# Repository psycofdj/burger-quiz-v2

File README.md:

<!-- markdown-toc start - Don't edit this section. Run M-x markdown-toc-refresh-toc -->
**Table of Contents**

- [Hardware](#hardware)
    - [Global Schematics](#global-schematics)
    - [Ready to solder PCB](#ready-to-solder-pcb)
- [Construction](#construction)
    - [Global design](#global-design)
    - [Components](#components)
- [Installation](#installation)

<!-- markdown-toc end -->

## Hardware

### Global Schematics

Sources for global schematics are [here](./kicad/board)

### Ready to solder PCB

Sources for ready-to-solder PCB are [here](./kicad/pcb)

## Construction

### Global design

Sources for desk design are [here](./sketcup)

### Components

- 22.99€,  3 x LCD displays: https://www.amazon.fr/dp/B07V5K3ZVB?ref=ppx_yo2ov_dt_b_product_details&th=1
- 8.99€,  15 x 3.3V to 5V signal converter: https://www.amazon.fr/dp/B082F6BSB5?psc=1&ref=ppx_yo2ov_dt_b_product_details
- 8.58€,   1 x LED kit: https://www.amazon.fr/dp/B08S2W74K7?ref=ppx_yo2ov_dt_b_product_details&th=1
- 10.99€,  1 x Flat cable: https://www.amazon.fr/dp/B082WZC56B?psc=1&ref=ppx_yo2ov_dt_b_product_details
- 11.99€,  1 x Connector kit: https://www.amazon.fr/dp/B089LZ14WB?psc=1&ref=ppx_yo2ov_dt_b_product_details
- 66.50€,  1 x Rasberry PI 4 model B: https://www.kubii.com/en/raspberry-pi-boards/2772-raspberry-pi-4-model-b-4gb-3272496309333.html
- 7,49 €,  1 x 16GB microSD: https://www.amazon.fr/dp/B07DVG12SF?psc=1&ref=ppx_yo2ov_dt_b_product_details
- 18.59€,  1 x USB Speader: https://www.amazon.fr/Umitive-Haut-Parleur-dOrdinateur-Compatibilit%C3%A9-Antid%C3%A9rapante/dp/B08JTRML6R/ref=sr_1_7?keywords=enceinte+usb&qid=1697275415&sr=8-7
- 38,27€, 13 x Custom made 5v LED push switches: https://fr.aliexpress.com/item/4000098893464.html?spm=a2g0o.order_list.order_list_main.10.21ef5e5b7tX8DX&gatewayAdapt=glo2fra

## Installation

Sources for software are [here](./bquiz)

- Enable primary I2C port (/dev/i2c-1)

```
$ sudo raspi-config
(select 3. Interface options)
(select I5. I2C)
(select yes)
```

- Enable secondary I2C port (/dev/i2c-0)

```
cat /boot/config.txt
...
dtparam=i2c_arm=on
dtparam=i2c_vc=on
...
```

- Check I2C ports

```
 # package to test gpio port
 sudo apt install i2c-dev i2c-tools

 # check i2c ports, should have 27 on
 i2cdetect -y 1
 i2cdetect -y 0
```

- Install sound support

```
 sudo apt-get install pulseaudio pulseaudio-utils python3-vlc
```

- Configure default pulseaudio sink

```
 pactl set-default-sink alsa_output.usb-C-Media_Electronics_Inc._USB_Audio_Device-00.analog-stereo
```

- Install software as user startup service

```
 # install bquiz cli to ~/.local/bin
 python3 -m pip install .

 # install user systemd unit
 mkdir -p ~/.config/systemd/user
 ln -s $(pwd)/systemd/user/bquiz.service ~/.config/systemd/
 systemctl --user enable bquiz.service

 # run bquiz
 systemctl --user start bquiz.service
```

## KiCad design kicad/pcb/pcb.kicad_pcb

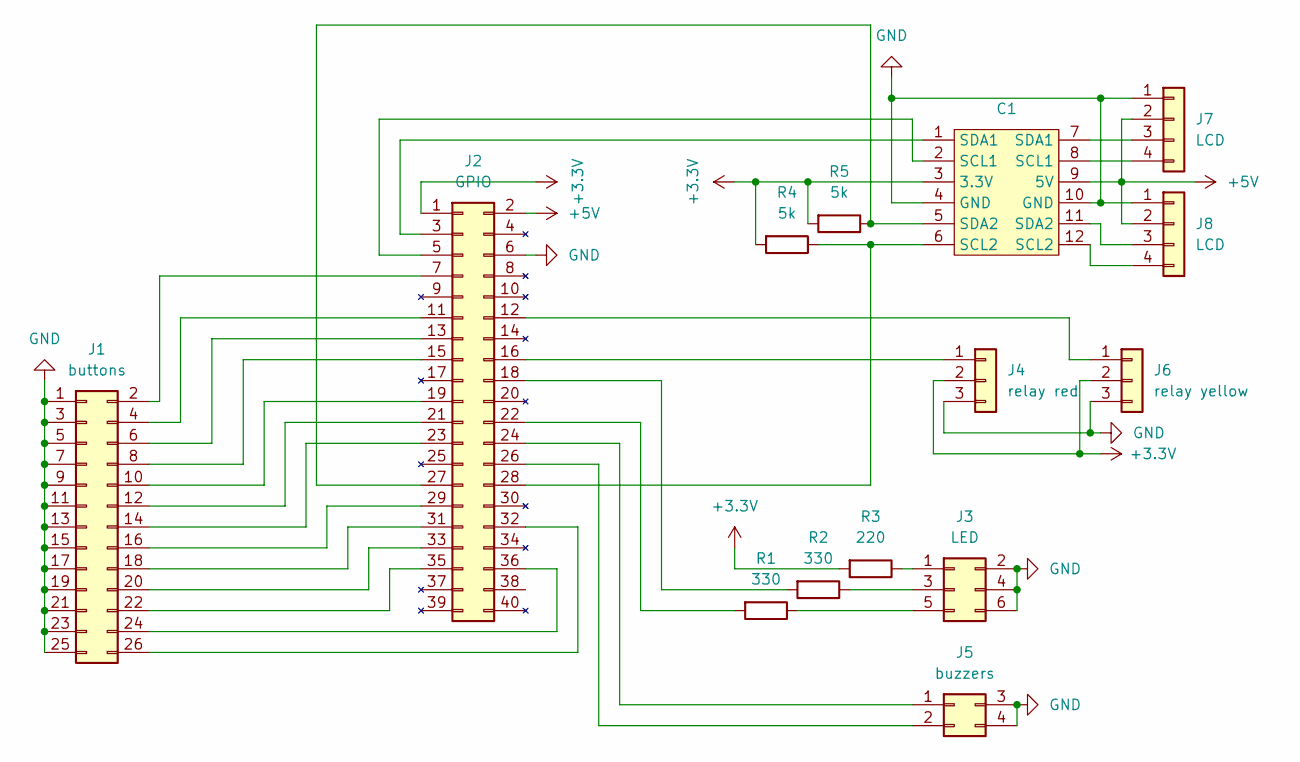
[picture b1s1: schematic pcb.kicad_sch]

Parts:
C1: Converter_3.3v_5v_i2c
J1: buttons; PinHeader_2x13_P2.54mm_Vertical
J2: GPIO; PinSocket_2x20_P2.54mm_Vertical
J3: LED; PinHeader_2x03_P2.54mm_Vertical
J4: relay red; PinHeader_1x03_P2.54mm_Vertical
J5: buzzers; PinHeader_2x02_P2.54mm_Vertical
J6: relay yellow; PinHeader_1x03_P2.54mm_Vertical
J7, J8: LCD; PinHeader_1x04_P2.54mm_Vertical
R1, R2: 330; R_Axial_DIN0204_L3.6mm_D1.6mm_P2.54mm_Vertical
R3: 220; R_Axial_DIN0204_L3.6mm_D1.6mm_P2.54mm_Vertical
R4, R5: 5k; R_Axial_DIN0204_L3.6mm_D1.6mm_P2.54mm_Vertical

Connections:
+3.3V: C1.3 (3.3V), J2.1 (3v3), J4.2, J6.2, R3.2, R4.2, R5.2
+5V: C1.9 (5V), J2.2 (5v0), J7.2 (VCC), J8.2 (VCC)
GND: C1.4 (GND), C1.10 (GND), J1.1 (reset), J1.3 (red+), J1.5 (red-), J1.7 (yellow+), J1.9 (yellow-), J1.11 (nuggets), J1.13 (selpoivre), J1.15 (menus), J1.17 (addition), J1.19 (sample1), J1.21 (sample2), J1.23 (sample3), J1.25 (sample4), J2.6 (GND), J3.2, J3.4, J3.6, J4.3, J5.3, J5.4, J6.3, J7.1 (GND), J8.1 (GND)
unnamed: C1.2 (SCL1), J2.5 (SCL1)
unnamed: C1.6 (SCL2), J2.28 (SCL2), R4.1
unnamed: C1.1 (SDA1), J2.3 (SDA1)
unnamed: C1.5 (SDA2), J2.27 (SDA2), R5.1
unnamed: J1.14 (selpoivre), J2.23 (wip14)
unnamed: J1.16 (menus), J2.29 (wip21)
unnamed: J1.18 (addition), J2.31 (wip22)
unnamed: J1.20 (sample1), J2.33 (wip23)
unnamed: J1.22 (sample2), J2.35 (wip24)
unnamed: J1.4 (red+), J2.11 (wpi0)
unnamed: J2.12 (wpi1), J6.1
unnamed: J1.6 (red-), J2.13 (wpi2)
unnamed: J1.8 (yellow+), J2.15 (wpi3)
unnamed: J2.16 (wpi4), J4.1
unnamed: J2.18 (wpi5), R2.2
unnamed: J2.22 (wpi6), R1.2
unnamed: J1.2 (reset), J2.7 (wpi7)
unnamed: J2.24 (wpi10), J5.1
unnamed: J2.26 (wpi11), J5.2
unnamed: J1.10 (yellow-), J2.19 (wpi12)
unnamed: J1.12 (nuggets), J2.21 (wpi13)
unnamed: J1.26 (sample4), J2.32 (wpi26)
unnamed: J1.24 (sample3), J2.36 (wpi27)
unnamed: J3.1, R3.1
unnamed: J3.3, R2.1
unnamed: J3.5, R1.1
unnamed: C1.8 (SCL1), J7.4 (SCL)
unnamed: C1.7 (SDA1), J7.3 (SDA)
unnamed: C1.12 (SCL2), J8.4 (SCL)
unnamed: C1.11 (SDA2), J8.3 (SDA)

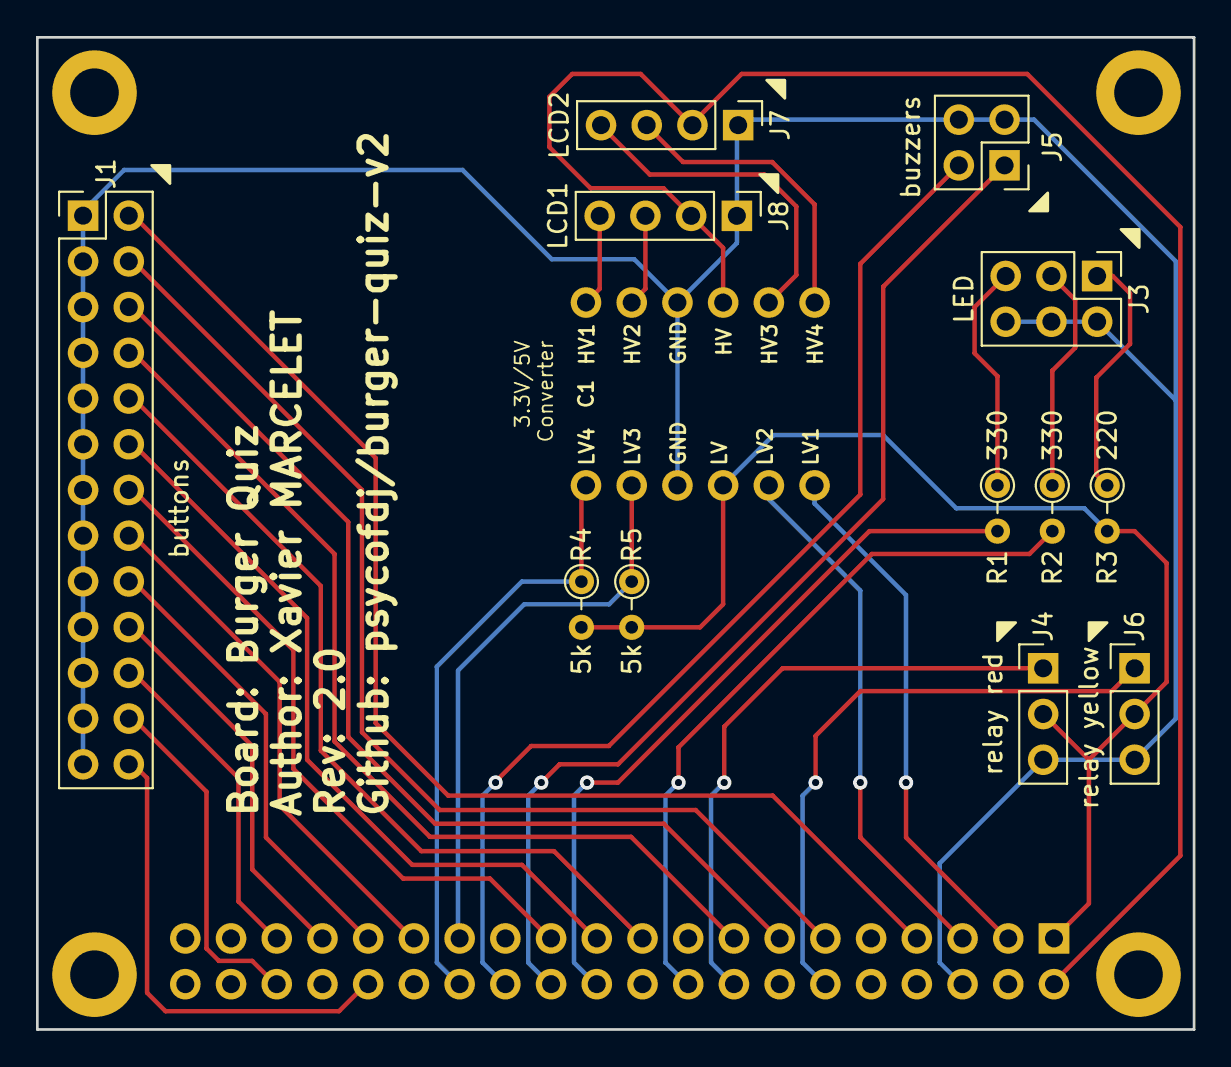
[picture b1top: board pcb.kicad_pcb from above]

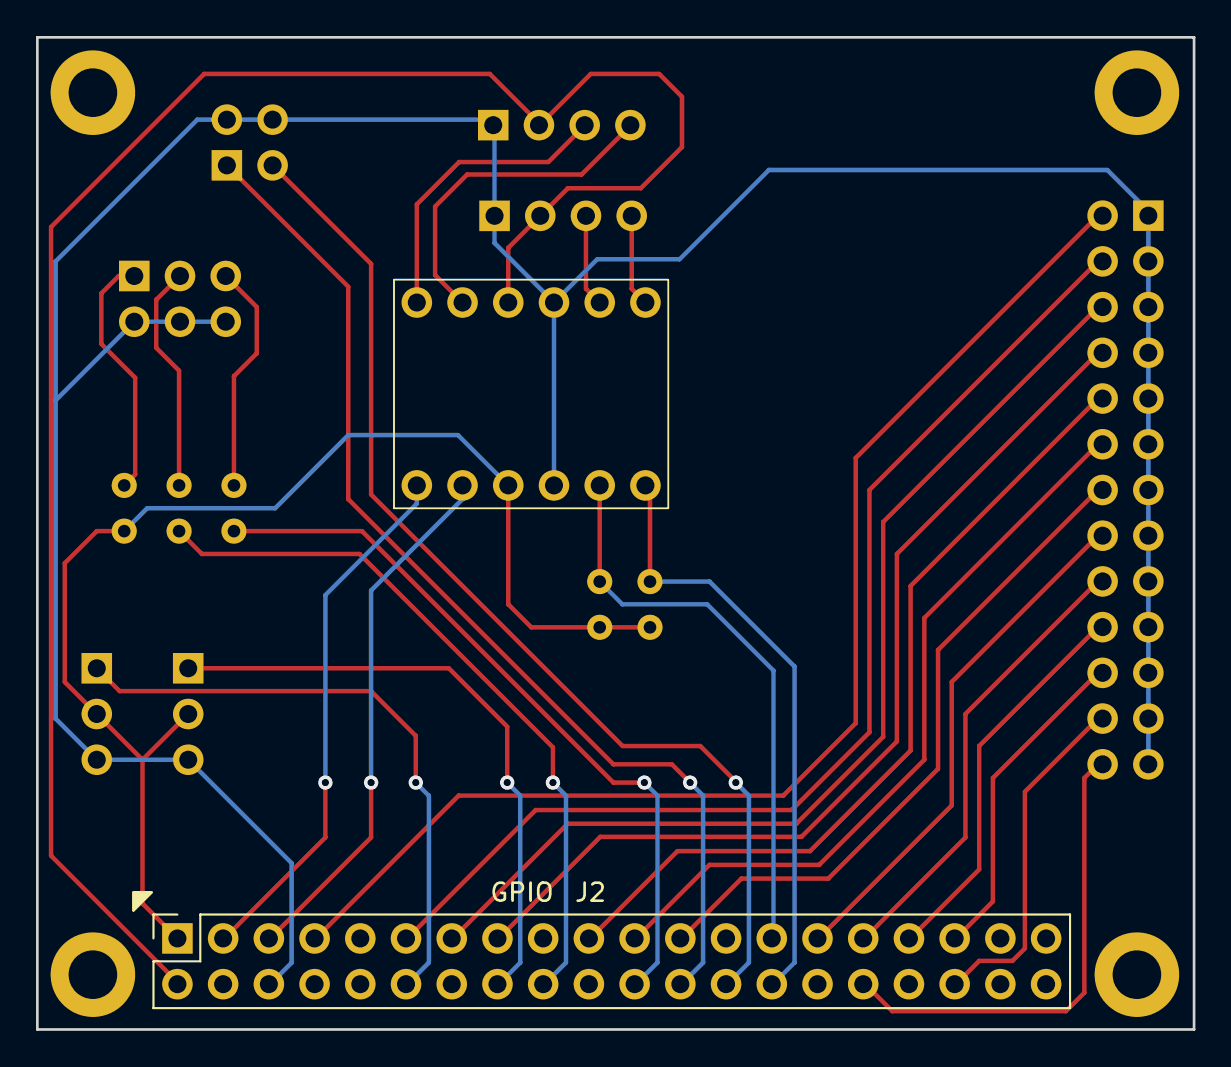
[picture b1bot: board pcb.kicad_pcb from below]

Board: 2 copper layers, 64.3 x 55.1 mm, 14 parts (2 on the bottom side), 33 nets.

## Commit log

2023-10-16 update systemd unit
2023-10-16 add skethup sources
2023-10-16 update pcb
2023-11-01 add questions and gui
2023-11-01 test1
